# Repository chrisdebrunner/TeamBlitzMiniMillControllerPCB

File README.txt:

EagleCAD files describing the PCB for the TeamBlitz mini-mill CNC controller.
TeamBlitz is a FIRST Robotics Challenge team 2083 from Conifer High School in
Conifer, CO.

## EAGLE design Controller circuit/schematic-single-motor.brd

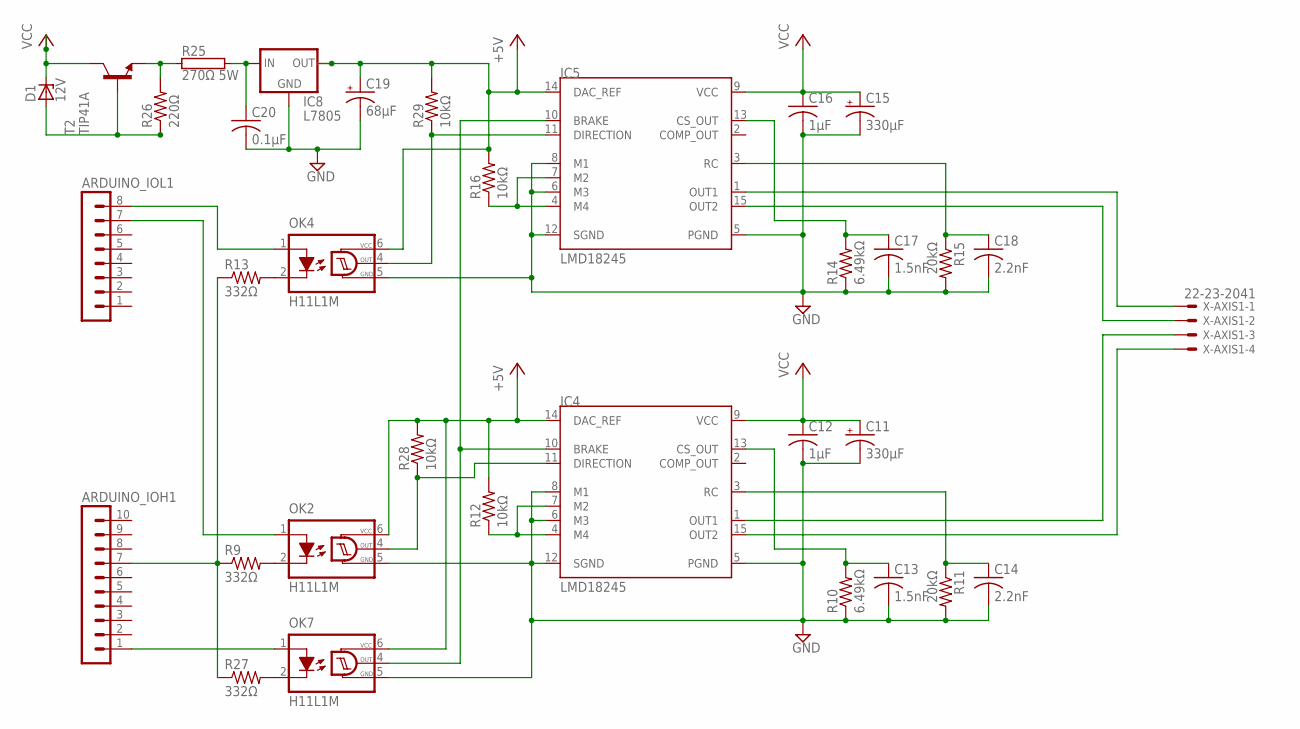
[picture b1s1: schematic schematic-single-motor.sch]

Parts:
ARDUINO_IOH1: MA10-1
ARDUINO_IOL1: MA08-1
C11, C15: 330µF; E5-13
C12, C16: 1µF; C050-024X044
C13, C17: 1.5nF; C050-024X044
C14, C18: 2.2nF; C050-024X044
C19: 68µF; E2,5-6
C20: 0.1µF; C102-054X133
D1: 12V; DO41Z10
IC4, IC5: LMD18245; MULTIWATT-15
IC8: L7805; 78XXS
OK2, OK4, OK7: H11L1M; DIL06
R9, R13, R27: 332Ω; 0204/7
R10, R14: 6.49kΩ; 0204/7
R11, R15: 20kΩ; 0204/7
R12, R16, R28, R29: 10kΩ; 0204/7
R25: 270Ω 5W; HPS523
R26: 220Ω; 0204/7
T2: TIP41A; TO202V
X-AXIS1: 22-23-2041

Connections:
+5V: C19.+, IC4.14 (DAC_REF), IC5.14 (DAC_REF), IC8.OUT, OK2.6 (VCC), OK4.6 (VCC), OK7.6 (VCC), R12.2, R16.2, R28.2, R29.2
GND: C11.-, C12.2, C13.2, C14.2, C15.-, C16.2, C17.2, C18.2, C19.-, C20.2, IC4.5 (PGND), IC4.6 (M3), IC4.8 (M1), IC4.12 (SGND), IC5.5 (PGND), IC5.6 (M3), IC5.8 (M1), IC5.12 (SGND), IC8.GND, OK2.5 (GND), OK4.5 (GND), OK7.5 (GND), R10.1, R11.2, R14.1, R15.2
unnamed: C13.1, IC4.13 (CS_OUT), R10.2
unnamed: C14.1, IC4.3 (RC), R11.1
unnamed: IC4.4 (M4), IC4.7 (M2), R12.1
unnamed: IC5.11 (DIRECTION), OK4.4 (OUT), R29.1
unnamed: C17.1, IC5.13 (CS_OUT), R14.2
unnamed: C18.1, IC5.3 (RC), R15.1
unnamed: IC5.4 (M4), IC5.7 (M2), R16.1
unnamed: IC5.1 (OUT1), X-AXIS1.1
unnamed: IC5.15 (OUT2), X-AXIS1.2
unnamed: IC4.1 (OUT1), X-AXIS1.3
unnamed: IC4.15 (OUT2), X-AXIS1.4
unnamed: ARDUINO_IOL1.7, OK2.1 (A)
unnamed: ARDUINO_IOH1.7, R9.1, R13.1, R27.1
unnamed: OK2.2 (C), R9.2
unnamed: OK4.2 (C), R13.2
unnamed: ARDUINO_IOL1.8, OK4.1 (A)
unnamed: D1.A, R26.1, T2.3 (B)
unnamed: R25.1, R26.2, T2.1 (E)
unnamed: C20.1, IC8.IN, R25.2
unnamed: OK7.2 (C), R27.2
unnamed: ARDUINO_IOH1.1, OK7.1 (A)
unnamed: IC4.10 (BRAKE), IC5.10 (BRAKE), OK7.4 (OUT)
unnamed: IC4.11 (DIRECTION), OK2.4 (OUT), R28.1
VCC: C11.+, C12.1, C15.+, C16.1, D1.C, IC4.9 (VCC), IC5.9 (VCC), T2.2 (C)

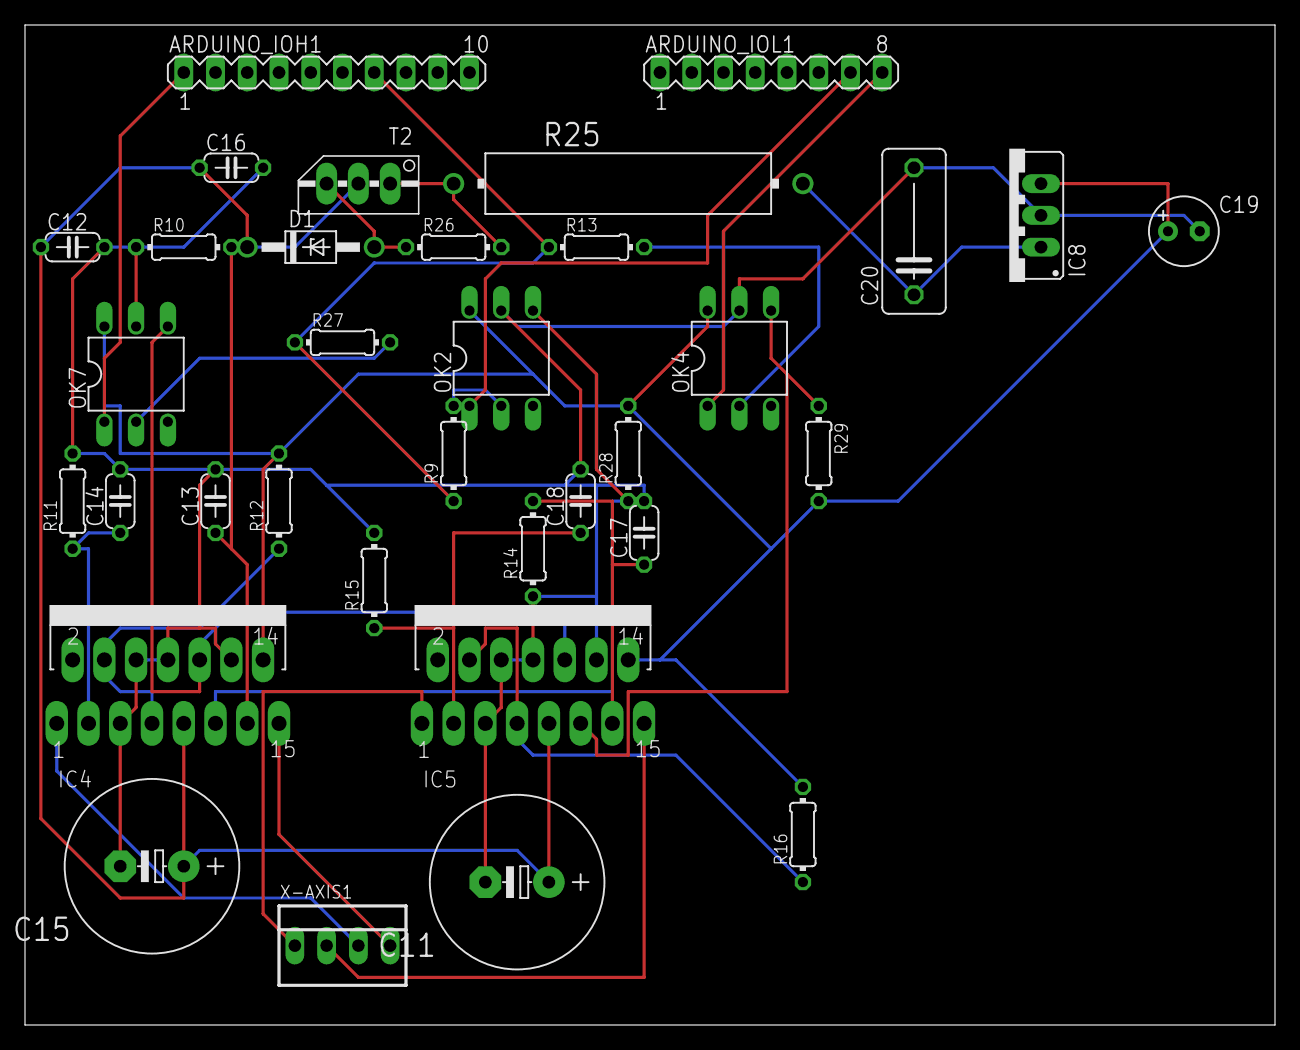
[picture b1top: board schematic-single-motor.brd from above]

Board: 2 copper layers, 100.0 x 80.0 mm, 34 parts (0 on the bottom side), 26 nets.

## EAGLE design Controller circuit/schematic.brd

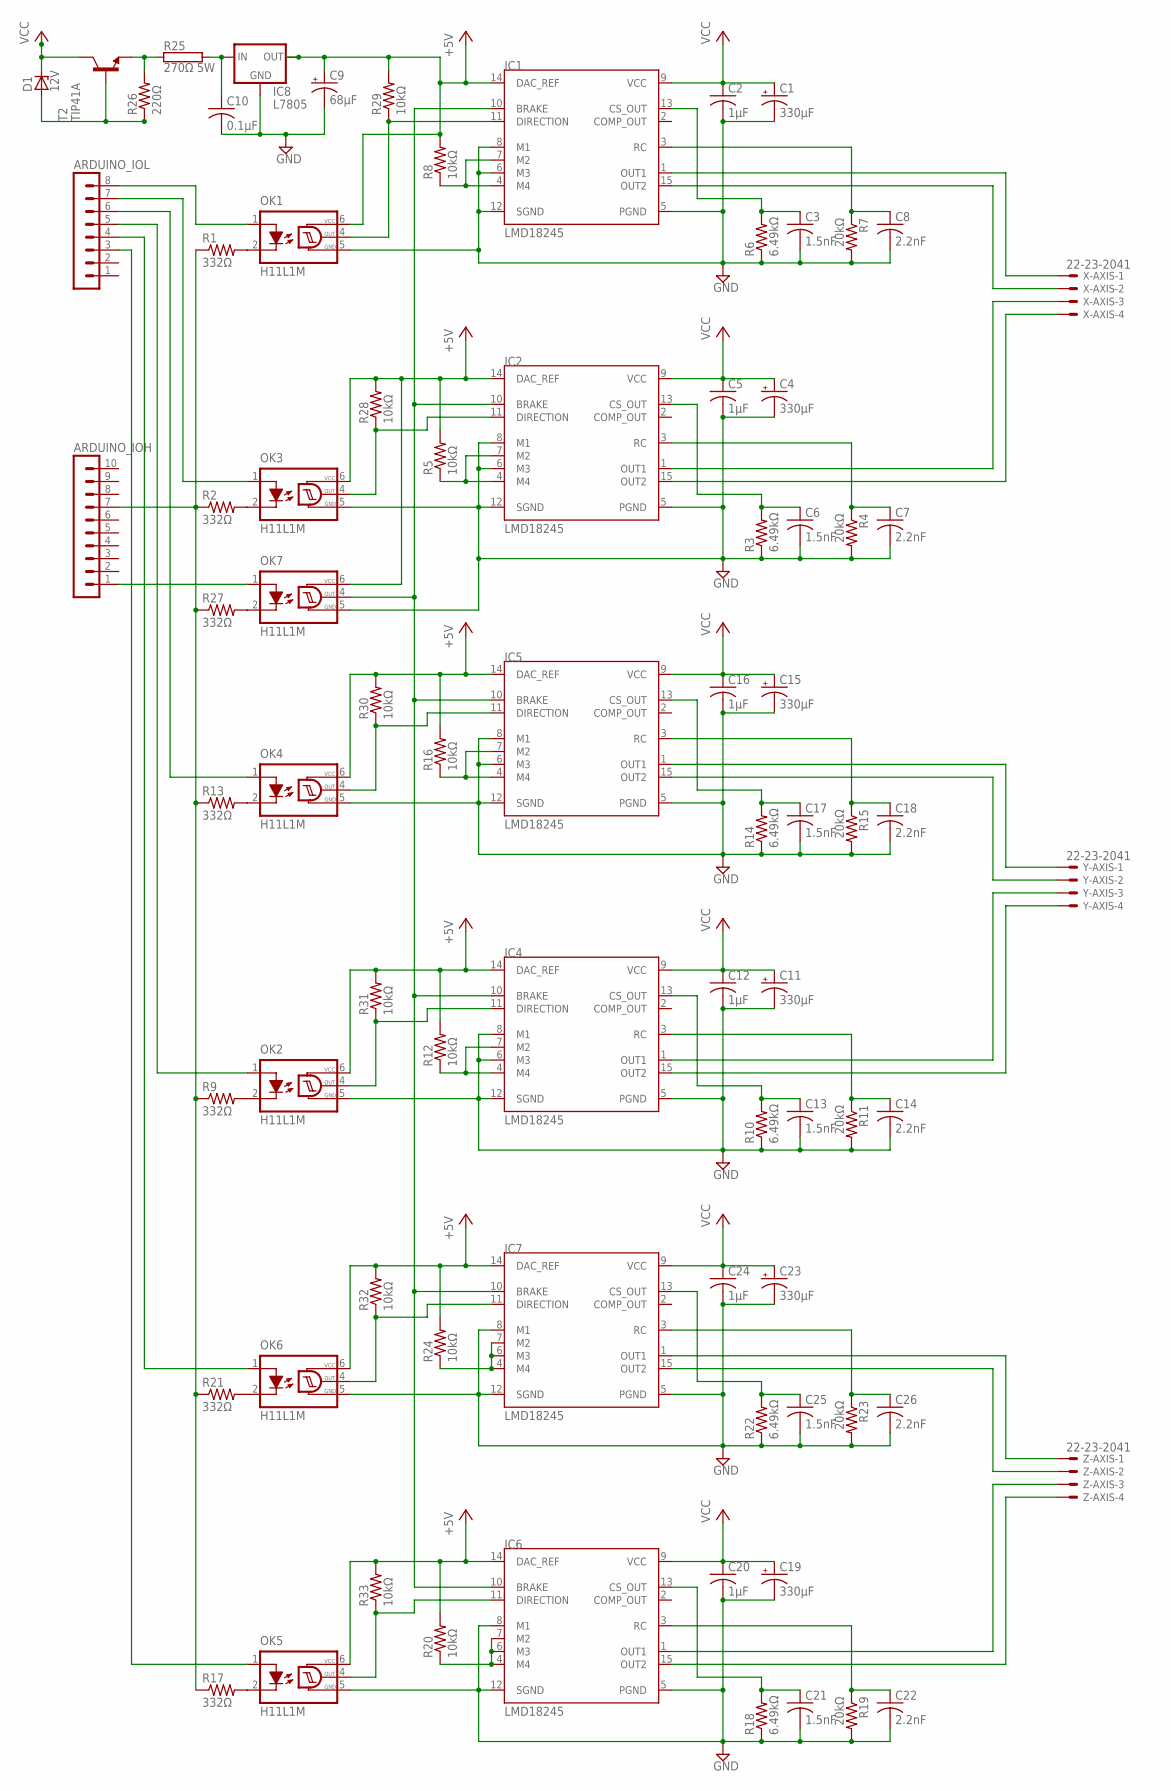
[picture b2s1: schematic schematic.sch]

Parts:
ARDUINO_IOH: MA10-1
ARDUINO_IOL: MA08-1
C1, C4, C11, C15, C19, C23: 330µF; E5-13
C2, C5, C12, C16, C20, C24: 1µF; C050-024X044
C3, C6, C13, C17, C21, C25: 1.5nF; C050-024X044
C7, C8, C14, C18, C22, C26: 2.2nF; C050-024X044
C9: 68µF; E2,5-6
C10: 0.1µF; C102-054X133
D1: 12V; DO41Z10
IC1, IC2, IC4, IC5, IC6, IC7: LMD18245; MULTIWATT-15
IC8: L7805; 78XXS
OK1, OK2, OK3, OK4, OK5, OK6, OK7: H11L1M; DIL06
R1, R2, R9, R13, R17, R21, R27: 332Ω; 0204/7
R3, R6, R10, R14, R18, R22: 6.49kΩ; 0204/7
R4, R7, R11, R15, R19, R23: 20kΩ; 0204/7
R5, R8, R12, R16, R20, R24, R28, R29, R30, R31, R32, R33: 10kΩ; 0204/7
R25: 270Ω 5W; HPS523
R26: 220Ω; 0204/7
T2: TIP41A; TO202V
X-AXIS: 22-23-2041
Y-AXIS: 22-23-2041
Z-AXIS: 22-23-2041

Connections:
+5V: C9.+, IC1.14 (DAC_REF), IC2.14 (DAC_REF), IC4.14 (DAC_REF), IC5.14 (DAC_REF), IC6.14 (DAC_REF), IC7.14 (DAC_REF), IC8.OUT, OK1.6 (VCC), OK2.6 (VCC), OK3.6 (VCC), OK4.6 (VCC), OK5.6 (VCC), OK6.6 (VCC), OK7.6 (VCC), R5.2, R8.2, R12.2, R16.2, R20.2, R24.2, R28.2, R29.2, R30.2, R31.2, R32.2, R33.2
GND: C1.-, C2.2, C3.2, C4.-, C5.2, C6.2, C7.2, C8.2, C9.-, C10.2, C11.-, C12.2, C13.2, C14.2, C15.-, C16.2, C17.2, C18.2, C19.-, C20.2, C21.2, C22.2, C23.-, C24.2, C25.2, C26.2, IC1.5 (PGND), IC1.6 (M3), IC1.8 (M1), IC1.12 (SGND), IC2.5 (PGND), IC2.6 (M3), IC2.8 (M1), IC2.12 (SGND), IC4.5 (PGND), IC4.6 (M3), IC4.8 (M1), IC4.12 (SGND), IC5.5 (PGND), IC5.6 (M3), IC5.8 (M1), IC5.12 (SGND), IC6.5 (PGND), IC6.8 (M1), IC6.12 (SGND), IC7.5 (PGND), IC7.8 (M1), IC7.12 (SGND), IC8.GND, OK1.5 (GND), OK2.5 (GND), OK3.5 (GND), OK4.5 (GND), OK5.5 (GND), OK6.5 (GND), OK7.5 (GND), R3.1, R4.2, R6.1, R7.2, R10.1, R11.2, R14.1, R15.2, R18.1, R19.2, R22.1, R23.2
unnamed: ARDUINO_IOH.7, R1.1, R2.1, R9.1, R13.1, R17.1, R21.1, R27.1
unnamed: IC1.11 (DIRECTION), OK1.4 (OUT), R29.1
unnamed: ARDUINO_IOL.8, OK1.1 (A)
unnamed: IC4.11 (DIRECTION), OK2.4 (OUT), R31.1
unnamed: C3.1, IC1.13 (CS_OUT), R6.2
unnamed: IC2.4 (M4), IC2.7 (M2), R5.1
unnamed: C8.1, IC1.3 (RC), R7.1
unnamed: IC1.4 (M4), IC1.7 (M2), R8.1
unnamed: IC7.11 (DIRECTION), OK6.4 (OUT), R32.1
unnamed: C6.1, IC2.13 (CS_OUT), R3.2
unnamed: ARDUINO_IOL.7, OK3.1 (A)
unnamed: C7.1, IC2.3 (RC), R4.1
unnamed: C13.1, IC4.13 (CS_OUT), R10.2
unnamed: C14.1, IC4.3 (RC), R11.1
unnamed: IC1.1 (OUT1), X-AXIS.1
unnamed: IC1.15 (OUT2), X-AXIS.2
unnamed: IC2.1 (OUT1), X-AXIS.3
unnamed: IC4.4 (M4), IC4.7 (M2), R12.1
unnamed: IC5.11 (DIRECTION), OK4.4 (OUT), R30.1
unnamed: IC2.15 (OUT2), X-AXIS.4
unnamed: OK3.2 (C), R2.2
unnamed: OK1.2 (C), R1.2
unnamed: C17.1, IC5.13 (CS_OUT), R14.2
unnamed: C18.1, IC5.3 (RC), R15.1
unnamed: IC5.4 (M4), IC5.7 (M2), R16.1
unnamed: IC5.1 (OUT1), Y-AXIS.1
unnamed: IC5.15 (OUT2), Y-AXIS.2
unnamed: IC4.1 (OUT1), Y-AXIS.3
unnamed: IC4.15 (OUT2), Y-AXIS.4
unnamed: ARDUINO_IOL.5, OK2.1 (A)
unnamed: IC7.4 (M4), IC7.6 (M3), IC7.7 (M2), R24.1
unnamed: OK2.2 (C), R9.2
unnamed: OK4.2 (C), R13.2
unnamed: ARDUINO_IOL.6, OK4.1 (A)
unnamed: IC6.11 (DIRECTION), OK5.4 (OUT), R33.1
unnamed: C21.1, IC6.13 (CS_OUT), R18.2
unnamed: C22.1, IC6.3 (RC), R19.1
unnamed: IC6.4 (M4), IC6.6 (M3), IC6.7 (M2), R20.1
unnamed: C25.1, IC7.13 (CS_OUT), R22.2
unnamed: C26.1, IC7.3 (RC), R23.1
unnamed: D1.A, R26.1, T2.3 (B)
unnamed: IC7.1 (OUT1), Z-AXIS.1
unnamed: IC7.15 (OUT2), Z-AXIS.2
unnamed: IC6.1 (OUT1), Z-AXIS.3
unnamed: IC6.15 (OUT2), Z-AXIS.4
unnamed: ARDUINO_IOL.3, OK5.1 (A)
unnamed: R25.1, R26.2, T2.1 (E)
unnamed: OK5.2 (C), R17.2
unnamed: OK6.2 (C), R21.2
unnamed: ARDUINO_IOL.4, OK6.1 (A)
unnamed: C10.1, IC8.IN, R25.2
unnamed: OK7.2 (C), R27.2
unnamed: ARDUINO_IOH.1, OK7.1 (A)
unnamed: IC1.10 (BRAKE), IC4.10 (BRAKE), IC5.10 (BRAKE), IC6.10 (BRAKE), IC7.10 (BRAKE), OK7.4 (OUT)
unnamed: IC2.11 (DIRECTION), OK3.4 (OUT), R28.1
VCC: C1.+, C2.1, C4.+, C5.1, C11.+, C12.1, C15.+, C16.1, C19.+, C20.1, C23.+, C24.1, D1.C, IC1.9 (VCC), IC2.9 (VCC), IC4.9 (VCC), IC5.9 (VCC), IC6.9 (VCC), IC7.9 (VCC), T2.2 (C)

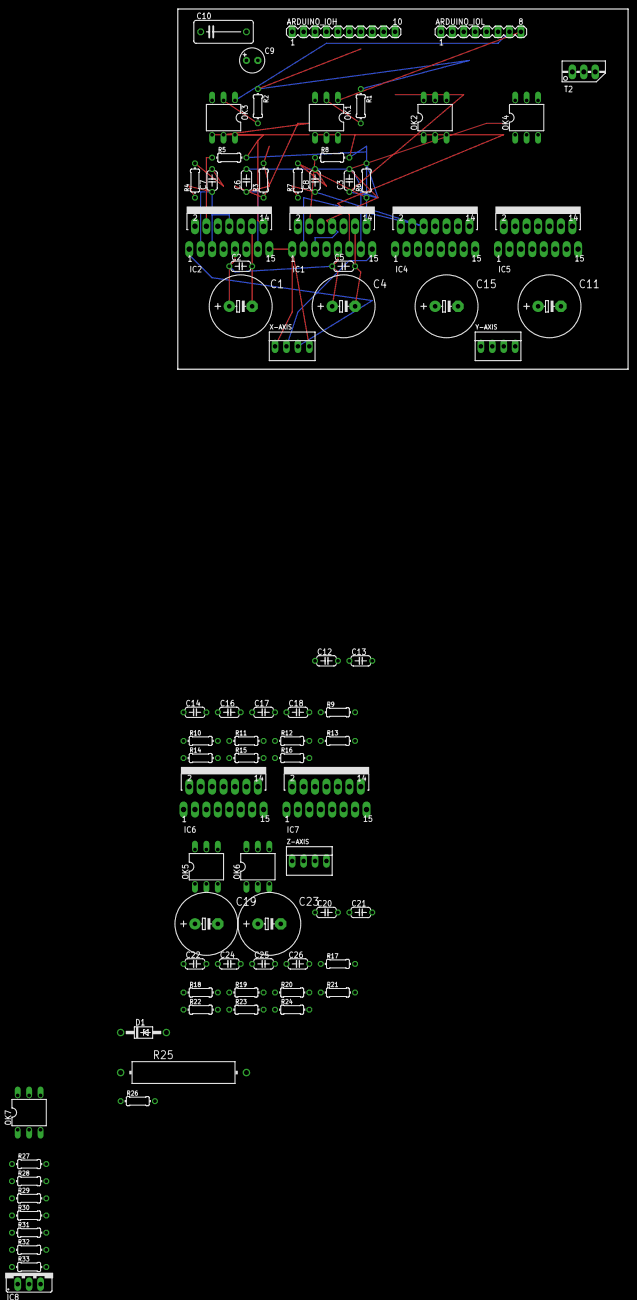
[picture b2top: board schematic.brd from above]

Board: 2 copper layers, 100.0 x 80.0 mm, 80 parts (0 on the bottom side), 58 nets.

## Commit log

2014-02-15 initial commit of MiniMill controller PC board
2014-02-15 reorganize libraries
2014-02-15 added README
